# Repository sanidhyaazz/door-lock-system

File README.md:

#RFID-Based Access Control System

The **Keyless Guardian 2.0)** is an advanced RFID-based access control system designed for secure and reliable door management in restricted environments. It uses an ESP32 for parallel card scanning, improved detection, and local storage of authorized users via SPIFFS, ensuring operation even without Wi-Fi, with automatic cloud synchronization when connectivity is restored.

The system features an Admin mode with an OLED display for onboard control, along with real-time monitoring through a Next.js dashboard with secure authentication. It integrates Discord API alerts and a camera feed for enhanced security and access tracking.

Built with two custom PCBs (indoor and outdoor units), the system includes safety features like emergency power input and a DIY BMS for backup. The enclosure is designed in Fusion 360 for a compact and professional finish, making it a robust and scalable solution for modern access control.

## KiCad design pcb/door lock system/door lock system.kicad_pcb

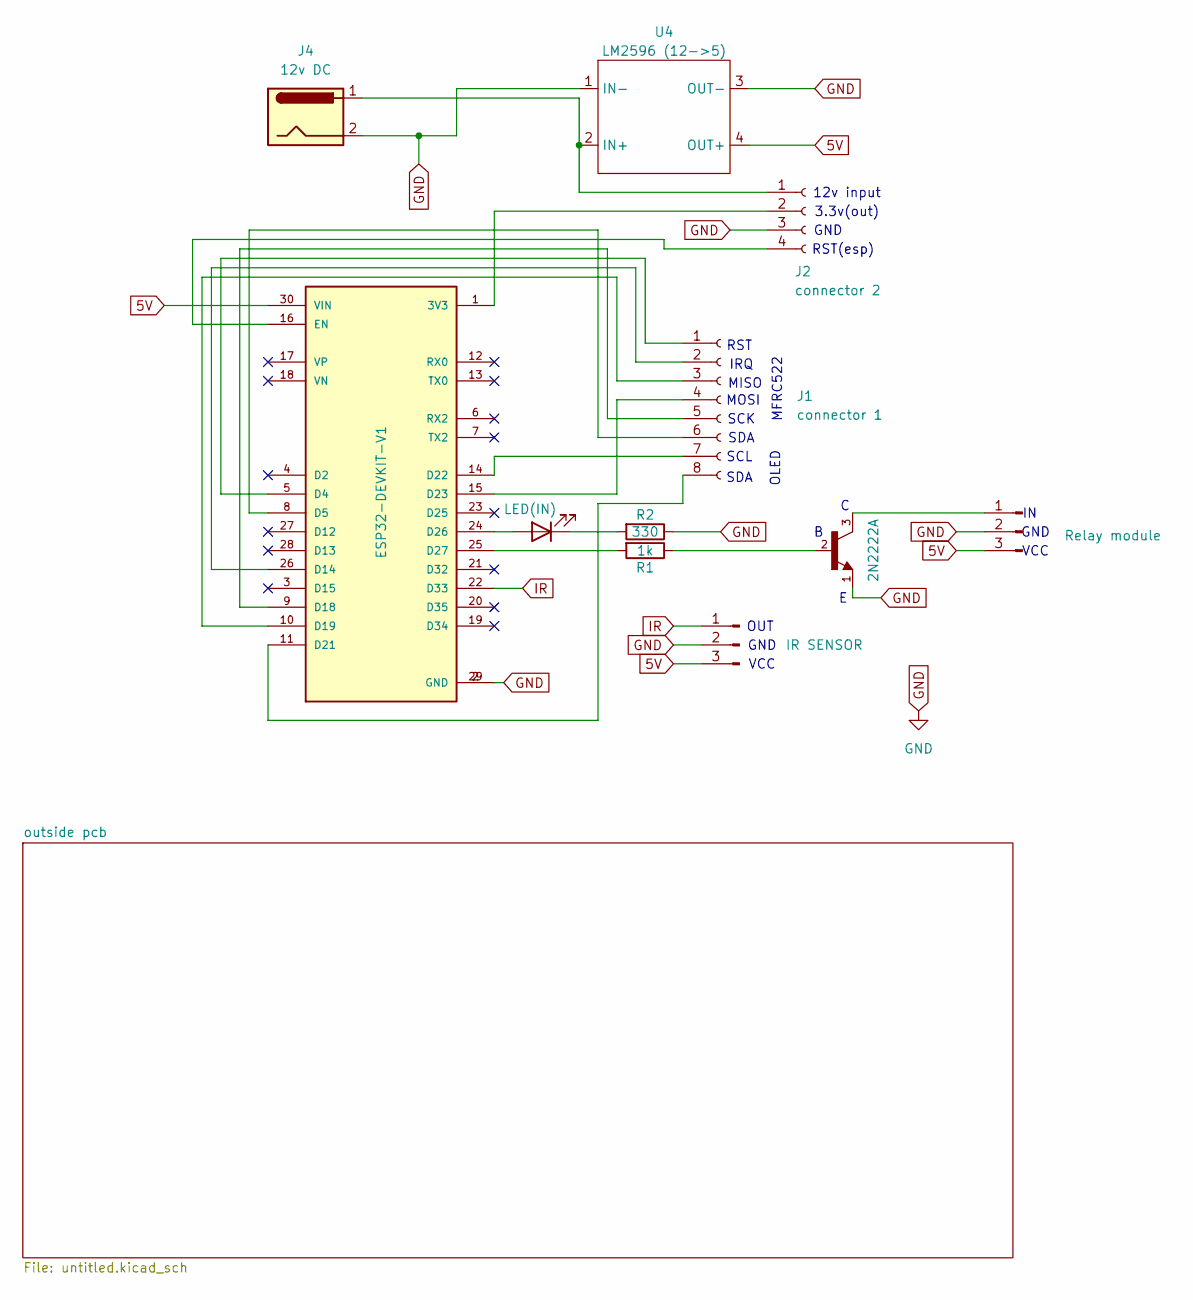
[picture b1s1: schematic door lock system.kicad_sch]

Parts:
D1: LED(IN); LED_D1.8mm_W3.3mm_H2.4mm
J1: connector 1; JST_EH_B8B-EH-A_1x08_P2.50mm_Vertical
J2: connector 2; JST_EH_B4B-EH-A_1x04_P2.50mm_Vertical
J3: Relay module; JST_EH_B3B-EH-A_1x03_P2.50mm_Vertical
J4: 12v DC; BarrelJack_SwitchcraftConxall_RAPC10U_Horizontal
J7: IR SENSOR; JST_EH_B3B-EH-A_1x03_P2.50mm_Vertical
Q1: 2N2222A; TO92254P470H750-3; PARTREV N/A
R1: 1k; R_Axial_DIN0207_L6.3mm_D2.5mm_P7.62mm_Horizontal
R2: 330; R_Axial_DIN0207_L6.3mm_D2.5mm_P7.62mm_Horizontal
U2: ESP32-DEVKIT-V1; MODULE_ESP32_DEVKIT_V1; PARTREV N/A
U4: LM2596 (12->5); LM2596

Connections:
5V: J3.3, J7.3, U2.30 (VIN), U4.4 (OUT+)
GND: J2.3, J3.2, J4.2, J7.2, Q1.1, R2.1, U2.2 (GND), U2.29 (GND), U4.1 (IN-), U4.3 (OUT-); also elsewhere on the board
IR: J7.1, U2.22 (D33)
unnamed: D1.2 (A), U2.24 (D26)
unnamed: D1.1 (K), R2.2
unnamed: J1.1, U2.5 (D4)
unnamed: J1.2, U2.26 (D14)
unnamed: J1.3, U2.10 (D19)
unnamed: J1.4, U2.15 (D23)
unnamed: J1.5, U2.9 (D18)
unnamed: J1.6, U2.8 (D5)
unnamed: J1.7, U2.14 (D22)
unnamed: J1.8, U2.11 (D21)
unnamed: J2.1, J4.1, U4.2 (IN+)
unnamed: J2.2, U2.1 (3V3)
unnamed: J2.4, U2.16 (EN)
unnamed: J3.1, Q1.3
unnamed: Q1.2, R1.1
unnamed: R1.2, U2.25 (D27)

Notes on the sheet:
GND
MFRC522
3.3v(out)
12v input
SCK
OLED
SDA
VCC
RST
OUT
IRQ
MISO
MOSI
RST(esp)
SCL

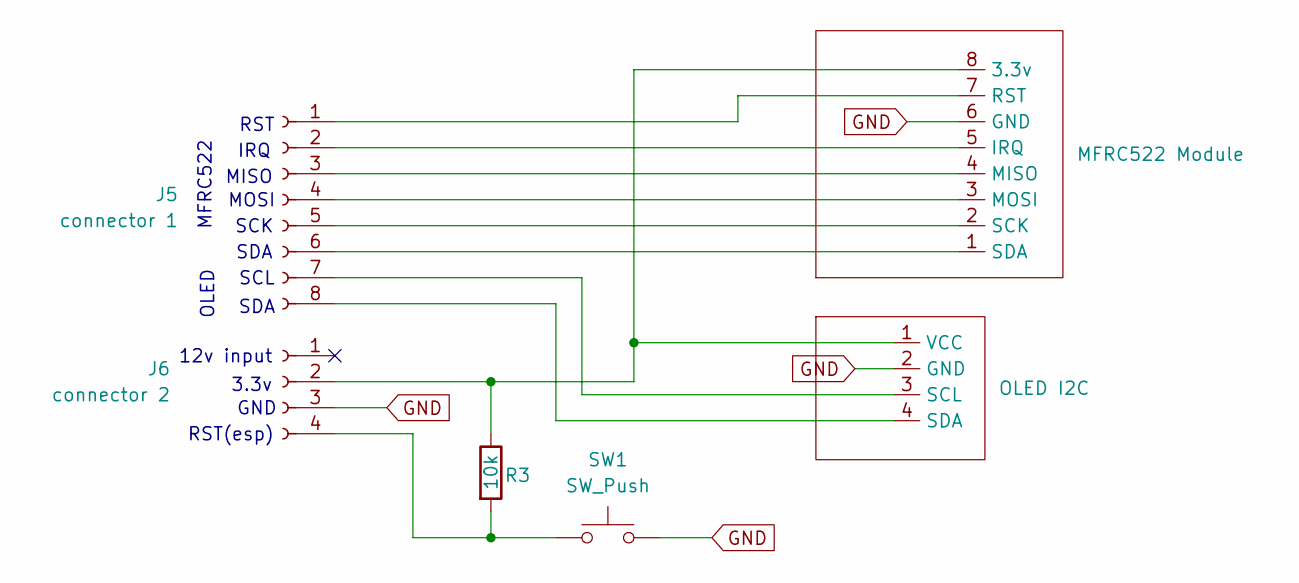
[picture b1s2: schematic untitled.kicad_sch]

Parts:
J5: connector 1; JST_EH_B8B-EH-A_1x08_P2.50mm_Vertical
J6: connector 2; JST_EH_B4B-EH-A_1x04_P2.50mm_Vertical
R3: 10k; R_Axial_DIN0207_L6.3mm_D2.5mm_P7.62mm_Horizontal
SW1: SW_Push; SW_PUSH_6mm_H4.3mm
U1: MFRC522 Module; PinHeader_1x08_P2.54mm_Vertical
U3: OLED I2C; PinHeader_1x04_P2.54mm_Vertical

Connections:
GND: J6.3, SW1.2, U1.6 (GND), U3.2 (GND); also elsewhere on the board
unnamed: J5.1, U1.7 (RST)
unnamed: J5.2, U1.5 (IRQ)
unnamed: J5.3, U1.4 (MISO)
unnamed: J5.4, U1.3 (MOSI)
unnamed: J5.5, U1.2 (SCK)
unnamed: J5.6, U1.1 (SDA)
unnamed: J5.7, U3.3 (SCL)
unnamed: J5.8, U3.4 (SDA)
unnamed: J6.2, R3.1, U1.8 (3.3v), U3.1 (VCC)
unnamed: J6.4, R3.2, SW1.1

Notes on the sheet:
MISO
12v input
3.3v
GND
OLED
RST(esp)
SCK
MOSI
MFRC522
IRQ
SDA
SCL
RST

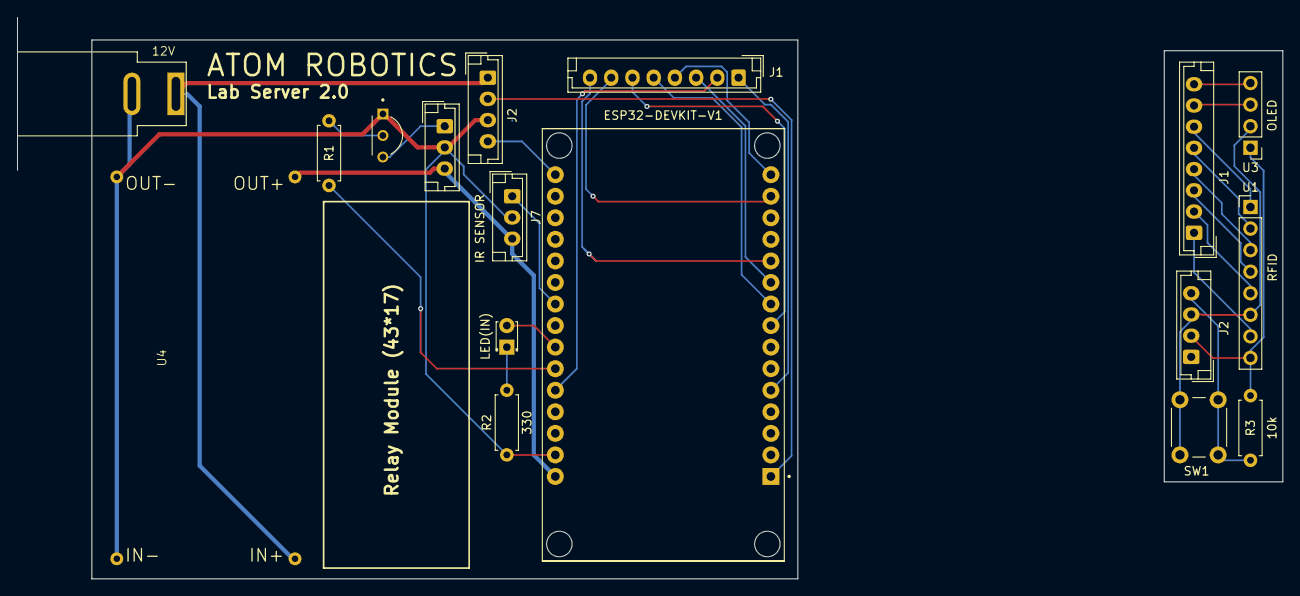
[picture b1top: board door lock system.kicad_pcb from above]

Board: 2 copper layers, 149.1 x 66.1 mm, 17 parts (0 on the bottom side), 29 nets.

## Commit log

2025-07-26 test code with Google Sheets
2025-07-26 flask added
2025-07-26 pcb files added and gitignore added
2025-08-05 Working Firebase code added
2025-08-05 firebase test code
2025-08-07 main working code added
2025-08-07 doc file added
2025-08-08 firebase background process
2025-08-08 doc added
2025-09-02 admin mode
2026-04-13 readme file added
